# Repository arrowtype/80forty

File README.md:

# 80forty Keyboard

The utility of an 80% keyboard in a 40% form factor.

Inspired by the design of the [OP-1 Synthesizer](https://teenage.engineering/store/op-1-field/), the explorative spirit of the 40% & 30% keyboard community (especially boards like ChonkyKong, CutiePie, and Ortho Cajal), and the tactile reference points and minimized finger-travel of many split, ergonomic keyboards. The 80forty was partly motivated by the appearance of [Deadline Studio DOYS keycaps](https://deadline.space/products/doys-keycaps), but it works with any MX-compatible keycaps.

The 80forty has a layout that is ortholinear and minimal, but still retains the keys that are helpful for everyday computing and specialized tasks like graphic design applications (i.e. arrow keys, bottom mod keys, and outer columns allowing for e.g. dedicated shift and backspace keys). It also allows either a knob or a 2x2 macropad above the arrow keys.

Supports low-profile KS33 switches (with hotswap sockets) as well as MX switches (soldered/mill-maxed).

## V1 Case Designs

Version 1 uses either a stacked acrylic or ”skeleton” FR4 plate design.

While the PCB supports either KS33 or MX switches, the current case designs have only been settled for the KS33 switches. MX switches require more space, and would likely require larger middle case layers.

### Stacked Acrylic Case

This case uses the standard FR4 top plate of the 80forty, and sandwiches it in a few layers of 5mm, lasercut acrylic.

### Skeleton FR4 Case

This case uses the standard FR4 top and bottom plates of the 80forty, with standoffs providing middle separation for the switches.

## Configuration Options

Configurable with either 1 large knob or 4 macro keys.

## Keymaps

80forty is configurable in Vial, so the keymap can be whatever you want! However, here are two example layouts to show what might be common approaches to such a keyboard.

The 2-unit spacebars are intended to serve double duty: to input `Space` when tapped, or to shift to respective layers when held.

Vial/QMK also allow for “key combos.” So, for instance, it is possible to forgo a dedicated `Escape` key and instead assign this to `Tilde` + `Q`.

## Future Vision

The project was conceived to allow a sleek, low-profile, CNC aluminum case design. This is still a goal, but there is no current timeline for this version.

In the slightly nearer term, the intention is to prototype this case with 3D printing. If anyone out there is interested in creating this 3D case and contributing it to the project, let us know in the issues or in a pull request!

## Credits

Concept, layout, case design, and PCB graphics by Stephen Nixon / ArrowType.

Engineering, code, and PCB specifications and ordering by Noah Kiser / Kiser Designs.

## To be continued!

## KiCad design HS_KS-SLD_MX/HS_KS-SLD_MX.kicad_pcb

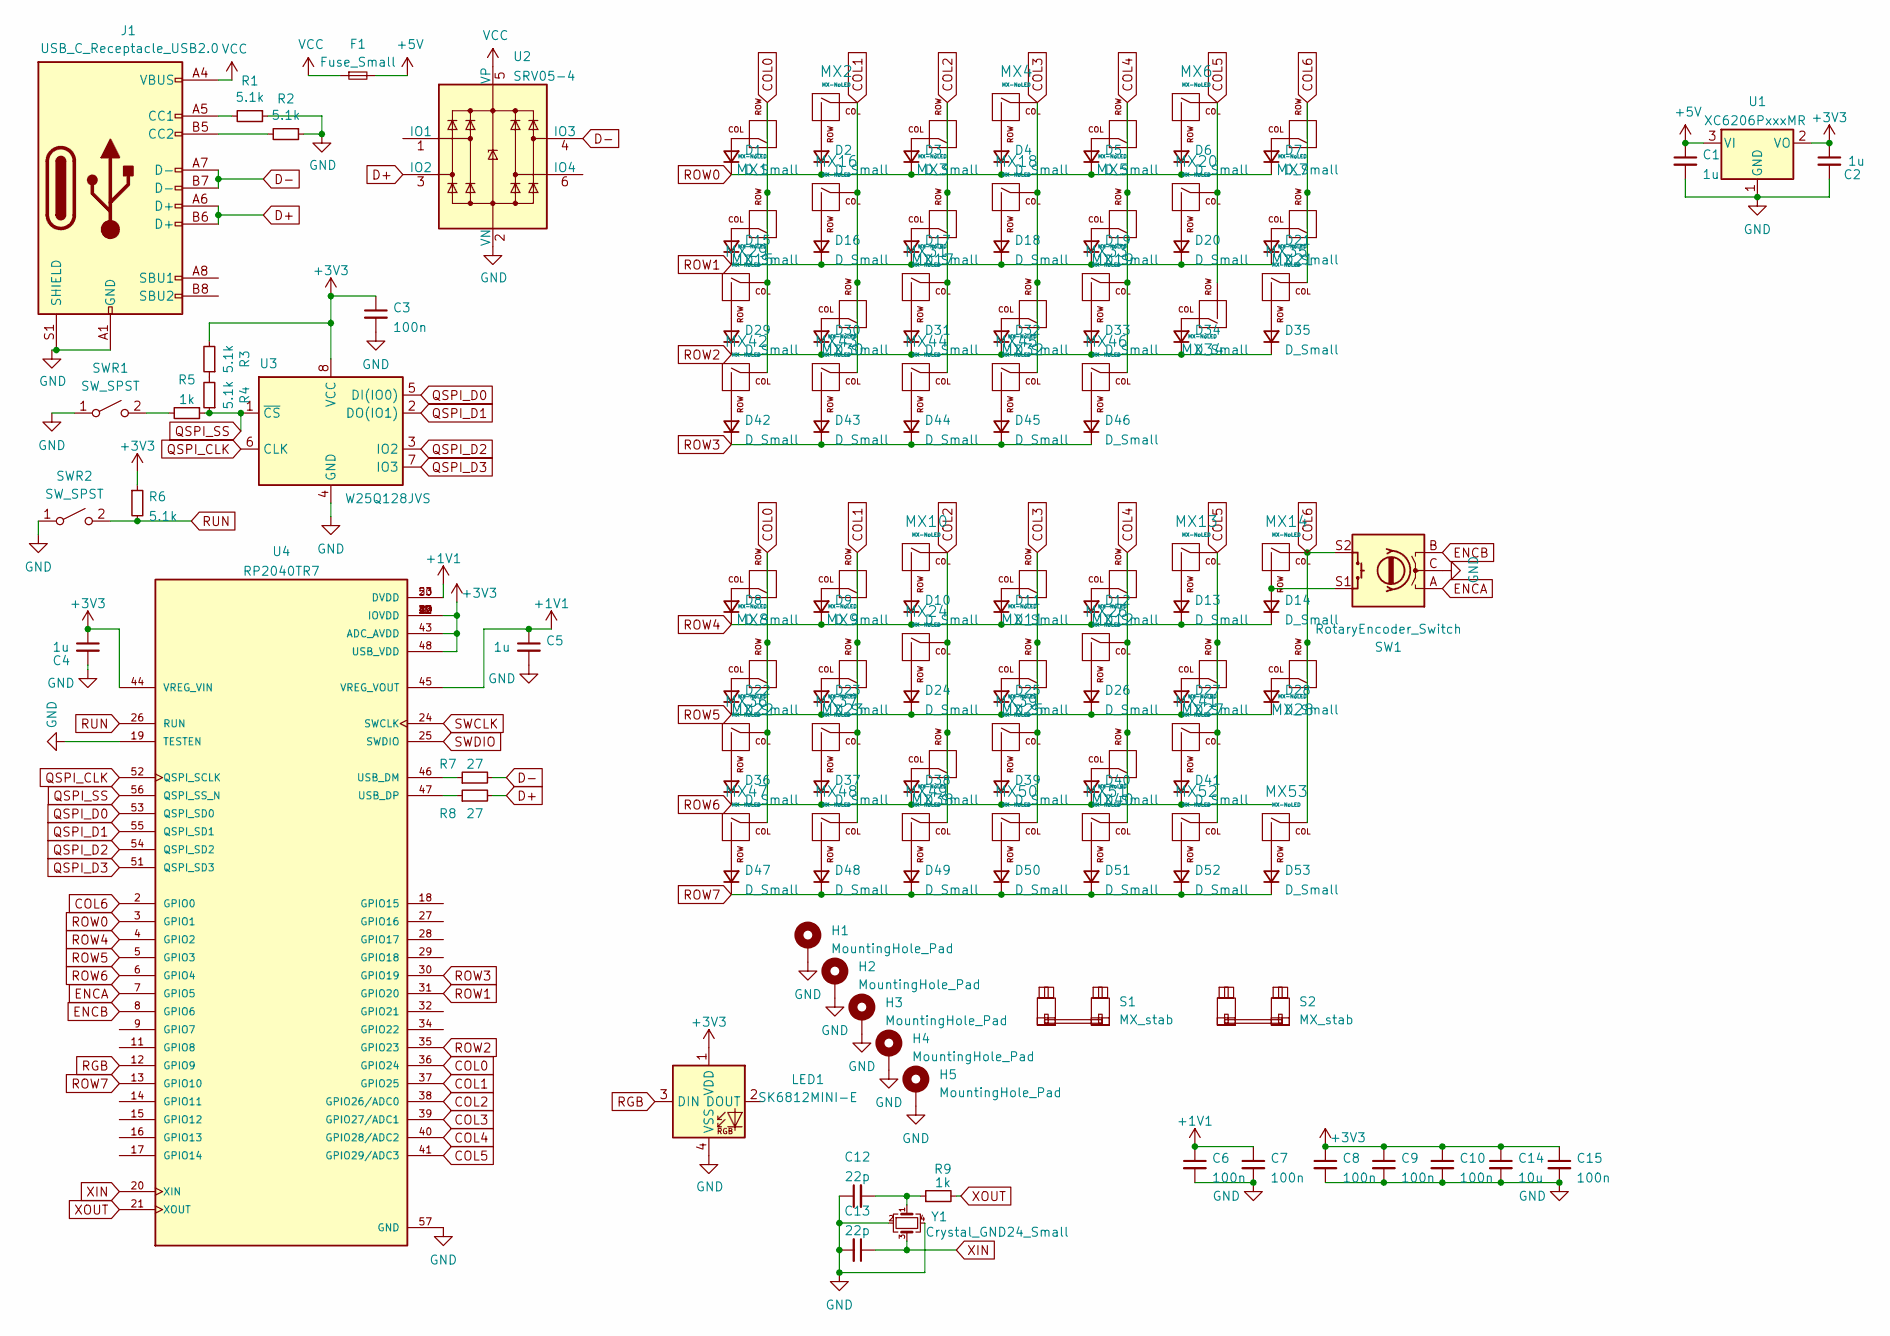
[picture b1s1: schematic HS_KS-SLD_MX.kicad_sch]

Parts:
C1, C2, C4, C5: 1u; C_0402_1005Metric
C3, C6, C7, C8, C9, C10, C15: 100n; C_0402_1005Metric
C12, C13: 22p; C_0402_1005Metric
C14: 10u; C_0402_1005Metric
D1, D2, D3, D4, D5, D6, D7, D8, D9, D10, D11, D12, D13, D14, D15, D16, D17, D18, D19, D20, D21, D22, D23, D24, D25, D26, D27, D28, D29, D30, D31, D32, D33, D34, D35, D36, D37, D38, D39, D40, D41, D42, D43, D44, D45, D46, D47, D48, D49, D50, D51, D52, D53: D_Small; D_SOD-123
F1: Fuse_Small; Fuse_1206_3216Metric
H1, H2, H3, H4, H5: MountingHole_Pad; MountingHole_2.2mm_M2_Pad_TopOnly
J1: USB_C_Receptacle_USB2.0; USB_C_Receptacle_HRO_TYPE-C-31-M-12
LED1: SK6812MINI-E; LED_6028R
MX1, MX2, MX3, MX4, MX5, MX6, MX7, MX8, MX9, MX10, MX11, MX12, MX13, MX14, MX15, MX16, MX17, MX18, MX19, MX20, MX21, MX22, MX23, MX24, MX25, MX26, MX27, MX28, MX29, MX30, MX31, MX32, MX33, MX34, MX35, MX36, MX37, MX38, MX39, MX40, MX41, MX42, MX43, MX44, MX45, MX46, MX47, MX48, MX49, MX50, MX51, MX52, MX53: MX-NoLED; HS-KS-33_Soldered-MX
R1, R2, R3, R4, R6: 5.1k; R_0402_1005Metric
R5, R9: 1k; R_0402_1005Metric
R7, R8: 27; R_0402_1005Metric
S1, S2: MX_stab; STAB_MX_P_2u
SW1: RotaryEncoder_Switch; RotaryEncoder_Alps_EC11E-Switch_Vertical_H20mm
SWR1, SWR2: SW_SPST; SW_SPST_TL3342
U1: XC6206PxxxMR; SOT-23
U2: SRV05-4; SOT-23-6-routable
U3: W25Q128JVS; SOIC-8_5.23x5.23mm_P1.27mm
U4: RP2040TR7; QFN-56-1EP_7x7mm_P0.4mm_EP3.2x3.2mm; PARTREV 1.7.1
Y1: Crystal_GND24_Small; Crystal_SMD_3225-4Pin_3.2x2.5mm

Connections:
+1V1: C5.1, C6.1, C7.1, U4.23 (DVDD), U4.45 (VREG_VOUT), U4.50 (DVDD)
+3V3: C2.1, C3.1, C4.1, C8.1, C9.1, C10.1, C14.1, C15.1, LED1.1 (VDD), R3.2, R6.1, U1.2 (VO), U3.8 (VCC), U4.1 (IOVDD), U4.10 (IOVDD), U4.22 (IOVDD), U4.33 (IOVDD), U4.42 (IOVDD), U4.43 (ADC_AVDD), U4.44 (VREG_VIN), U4.48 (USB_VDD), U4.49 (IOVDD)
+5V: C1.1, F1.2, U1.3 (VI)
COL0: MX1.2 (ROW), MX8.2 (ROW), MX15.2 (ROW), MX22.2 (ROW), MX29.1 (COL), MX36.1 (COL), MX42.1 (COL), MX47.1 (COL), U4.36 (GPIO24)
COL1: MX2.1 (COL), MX9.2 (ROW), MX16.1 (COL), MX23.2 (ROW), MX30.2 (ROW), MX37.1 (COL), MX43.1 (COL), MX48.1 (COL), U4.37 (GPIO25)
COL2: MX3.2 (ROW), MX10.1 (COL), MX17.2 (ROW), MX24.1 (COL), MX31.1 (COL), MX38.2 (ROW), MX44.1 (COL), MX49.1 (COL), U4.38 (GPIO26/ADC0)
COL3: MX4.1 (COL), MX11.2 (ROW), MX18.1 (COL), MX25.2 (ROW), MX32.2 (ROW), MX39.1 (COL), MX45.1 (COL), MX50.1 (COL), U4.39 (GPIO27/ADC1)
COL4: MX5.2 (ROW), MX12.2 (ROW), MX19.2 (ROW), MX26.1 (COL), MX33.1 (COL), MX40.2 (ROW), MX46.1 (COL), MX51.1 (COL), U4.40 (GPIO28/ADC2)
COL5: MX6.1 (COL), MX13.1 (COL), MX20.1 (COL), MX27.2 (ROW), MX34.2 (ROW), MX41.1 (COL), MX52.1 (COL), U4.41 (GPIO29/ADC3)
COL6: MX7.2 (ROW), MX14.1 (COL), MX21.2 (ROW), MX28.2 (ROW), MX35.1 (COL), MX53.1 (COL), SW1.S2, U4.2 (GPIO0)
D+: J1.A6 (D+), J1.B6 (D+), R8.2, U2.3 (IO2)
D-: J1.A7 (D-), J1.B7 (D-), R7.2, U2.4 (IO3)
ENCA: SW1.A, U4.7 (GPIO5)
ENCB: SW1.B, U4.8 (GPIO6)
GND: C1.2, C2.2, C3.2, C4.2, C5.2, C6.2, C7.2, C8.2, C9.2, C10.2, C12.1, C13.2, C14.2, C15.2, H1.1, H2.1, H3.1, H4.1, H5.1, J1.A1 (GND), J1.A12 (GND), J1.B1 (GND), J1.B12 (GND), J1.S1 (SHIELD), LED1.4 (VSS), R1.1, R2.1, SW1.C, SWR1.1 (A), SWR2.1 (A), U1.1 (GND), U2.2 (VN), U3.4 (GND), U4.19 (TESTEN), U4.57 (GND), Y1.2, Y1.4
unnamed: C12.2, R9.1, Y1.1
unnamed: D1.2 (A), MX1.1 (COL)
unnamed: D2.2 (A), MX2.2 (ROW)
unnamed: D3.2 (A), MX3.1 (COL)
unnamed: D4.2 (A), MX4.2 (ROW)
unnamed: D5.2 (A), MX5.1 (COL)
unnamed: D6.2 (A), MX6.2 (ROW)
unnamed: D7.2 (A), MX7.1 (COL)
unnamed: D8.2 (A), MX8.1 (COL)
unnamed: D9.2 (A), MX9.1 (COL)
unnamed: D10.2 (A), MX10.2 (ROW)
unnamed: D11.2 (A), MX11.1 (COL)
unnamed: D12.2 (A), MX12.1 (COL)
unnamed: D13.2 (A), MX13.2 (ROW)
unnamed: D14.2 (A), MX14.2 (ROW), SW1.S1
unnamed: D15.2 (A), MX15.1 (COL)
unnamed: D16.2 (A), MX16.2 (ROW)
unnamed: D17.2 (A), MX17.1 (COL)
unnamed: D18.2 (A), MX18.2 (ROW)
unnamed: D19.2 (A), MX19.1 (COL)
unnamed: D20.2 (A), MX20.2 (ROW)
unnamed: D21.2 (A), MX21.1 (COL)
unnamed: D22.2 (A), MX22.1 (COL)
unnamed: D23.2 (A), MX23.1 (COL)
unnamed: D24.2 (A), MX24.2 (ROW)
unnamed: D25.2 (A), MX25.1 (COL)
unnamed: D26.2 (A), MX26.2 (ROW)
unnamed: D27.2 (A), MX27.1 (COL)
unnamed: D28.2 (A), MX28.1 (COL)
unnamed: D29.2 (A), MX29.2 (ROW)
unnamed: D30.2 (A), MX30.1 (COL)
unnamed: D31.2 (A), MX31.2 (ROW)
unnamed: D32.2 (A), MX32.1 (COL)
unnamed: D33.2 (A), MX33.2 (ROW)
unnamed: D34.2 (A), MX34.1 (COL)
unnamed: D35.2 (A), MX35.2 (ROW)
unnamed: D36.2 (A), MX36.2 (ROW)
unnamed: D37.2 (A), MX37.2 (ROW)
unnamed: D38.2 (A), MX38.1 (COL)
unnamed: D39.2 (A), MX39.2 (ROW)
unnamed: D40.2 (A), MX40.1 (COL)
unnamed: D41.2 (A), MX41.2 (ROW)
unnamed: D42.2 (A), MX42.2 (ROW)
unnamed: D43.2 (A), MX43.2 (ROW)
unnamed: D44.2 (A), MX44.2 (ROW)
unnamed: D45.2 (A), MX45.2 (ROW)
unnamed: D46.2 (A), MX46.2 (ROW)
unnamed: D47.2 (A), MX47.2 (ROW)
unnamed: D48.2 (A), MX48.2 (ROW)
unnamed: D49.2 (A), MX49.2 (ROW)
unnamed: D50.2 (A), MX50.2 (ROW)
unnamed: D51.2 (A), MX51.2 (ROW)
unnamed: D52.2 (A), MX52.2 (ROW)
unnamed: D53.2 (A), MX53.2 (ROW)
unnamed: J1.A5 (CC1), R1.2
unnamed: J1.B5 (CC2), R2.2
unnamed: R3.1, R4.2
unnamed: R5.2, SWR1.2 (B)
unnamed: R7.1, U4.46 (USB_DM)
unnamed: R8.1, U4.47 (USB_DP)
QSPI_CLK: U3.6 (CLK), U4.52 (QSPI_SCLK)
QSPI_D0: U3.5 (DI(IO0)), U4.53 (QSPI_SD0)
QSPI_D1: U3.2 (DO(IO1)), U4.55 (QSPI_SD1)
QSPI_D2: U3.3 (IO2), U4.54 (QSPI_SD2)
QSPI_D3: U3.7 (IO3), U4.51 (QSPI_SD3)
QSPI_SS: R4.1, R5.1, U3.1 (~CS), U4.56 (QSPI_SS_N)
RGB: LED1.3 (DIN), U4.12 (GPIO9)
ROW0: D1.1 (K), D2.1 (K), D3.1 (K), D4.1 (K), D5.1 (K), D6.1 (K), D7.1 (K), U4.3 (GPIO1)
ROW1: D15.1 (K), D16.1 (K), D17.1 (K), D18.1 (K), D19.1 (K), D20.1 (K), D21.1 (K), U4.31 (GPIO20)
ROW2: D29.1 (K), D30.1 (K), D31.1 (K), D32.1 (K), D33.1 (K), D34.1 (K), D35.1 (K), U4.35 (GPIO23)
ROW3: D42.1 (K), D43.1 (K), D44.1 (K), D45.1 (K), D46.1 (K), U4.30 (GPIO19)
ROW4: D8.1 (K), D9.1 (K), D10.1 (K), D11.1 (K), D12.1 (K), D13.1 (K), D14.1 (K), U4.4 (GPIO2)
ROW5: D22.1 (K), D23.1 (K), D24.1 (K), D25.1 (K), D26.1 (K), D27.1 (K), D28.1 (K), U4.5 (GPIO3)
ROW6: D36.1 (K), D37.1 (K), D38.1 (K), D39.1 (K), D40.1 (K), D41.1 (K), U4.6 (GPIO4)
ROW7: D47.1 (K), D48.1 (K), D49.1 (K), D50.1 (K), D51.1 (K), D52.1 (K), D53.1 (K), U4.13 (GPIO10)
RUN: R6.2, SWR2.2 (B), U4.26 (RUN)
SWCLK: U4.24 (SWCLK)
SWDIO: U4.25 (SWDIO)
VCC: F1.1, J1.A4 (VBUS), J1.A9 (VBUS), J1.B4 (VBUS), J1.B9 (VBUS), U2.5 (VP)
XIN: C13.1, U4.20 (XIN), Y1.3
XOUT: R9.2, U4.21 (XOUT)

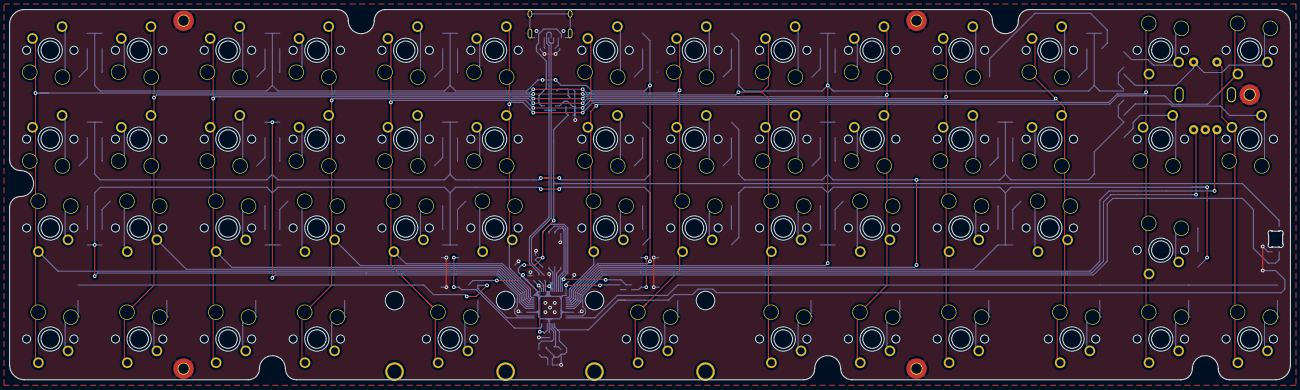
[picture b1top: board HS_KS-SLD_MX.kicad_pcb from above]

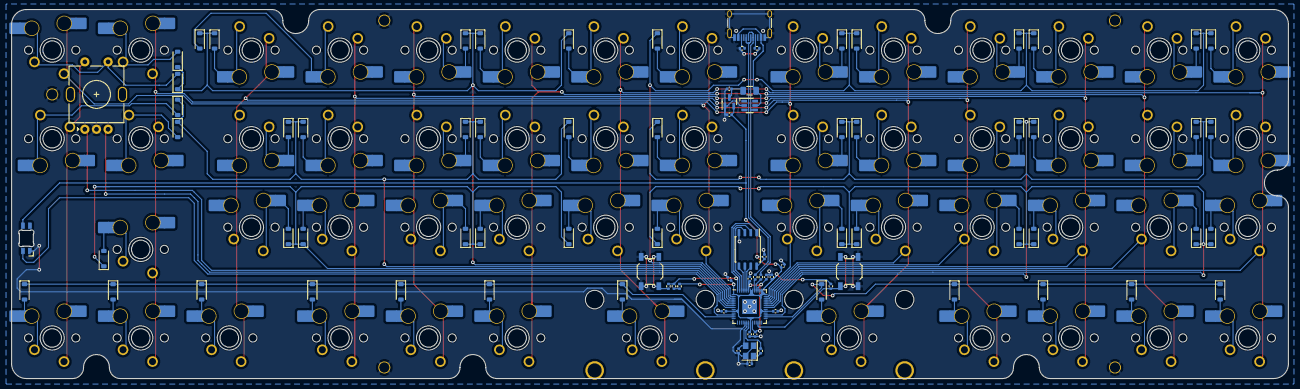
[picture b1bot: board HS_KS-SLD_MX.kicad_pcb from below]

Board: 2 copper layers, 274.6 x 79.4 mm, 147 parts (89 on the bottom side), 94 nets.

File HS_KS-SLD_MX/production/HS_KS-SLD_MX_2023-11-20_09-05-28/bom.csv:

Designator,Footprint,Quantity,Value,LCSC Part #
"C1, C2, C4, C5",402,4,1u,C52923
"C10, C15, C3, C6, C7, C8, C9",402,7,100n,C1525
"C12, C13",402,2,22p,C1562
C14,402,1,10u,C15525
"D1, D10, D11, D12, D13, D14, D15, D16, D17, D18, D19, D2, D20, D21, D22, D23, D24, D25, D26, D27, D28, D29, D3, D30, D31, D32, D33, D34, D35, D36, D37, D38, D39, D4, D40, D41, D42, D43, D44, D45, D46, D47, D48, D49, D5, D50, D51, D52, D53, D6, D7, D8, D9",D_SOD-123,53,D_Small,C81598
F1,1206,1,Fuse_Small,C883133
J1,USB_C_Receptacle_HRO_TYPE-C-31-M-12,1,USB_C_Receptacle_USB2.0,C165948
LED1,LED_6028R,1,SK6812MINI-E,C5149201
"R1, R2, R3, R4, R6",402,5,5.1k,C25905
"R5, R9",402,2,1k,C11702
"R7, R8",402,2,27,C25092
"SWR1, SWR2",SW_SPST_TL3342,2,SW_SPST,C318884
U1,SOT-23,1,XC6206PxxxMR,C5446
U2,SOT-23-6-routable,1,SRV05-4,C85364
U3,SOIC-8_5.23x5.23mm_P1.27mm,1,W25Q128JVS,C97521
U4,QFN-56-1EP_7x7mm_P0.4mm_EP3.2x3.2mm,1,RP2040TR7,C2040
Y1,Crystal_SMD_3225-4Pin_3.2x2.5mm,1,Crystal_GND24_Small,C2040

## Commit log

2023-08-02 Initial commit of PCB source, unfinished
2023-08-03 Update LICENSE
2023-08-03 routed rows
2023-08-03 A bit more routing
2023-08-03 almost done with columns
2023-08-03 add .gitignore to ignore .DS_Store
2023-08-03 Just a few more connections
2023-08-04 Completed MX PCB
2023-08-06 Add GLP_PCB, name fix
2023-08-23 lo-pro test production
2023-08-25 some changes
2023-10-31 add mx+gs hotswap PCB
2023-11-02 Routed, will DRC tomorrow
2023-11-03 remove unneeded PCB options
2023-11-05 add br00tal artwork
2023-11-05 tweak artwork for slightly better letter spacing
2023-11-05 add quick image of approximate artwork placement on PCB
2023-11-05 tweak artwork again
2023-11-06 Add SVGs
2023-11-12 add design for artwork placement
2023-11-12 outline text in artwork
2023-11-12 Move logos to Layer 1
2023-11-13 Added WIP graphics to PCB (and dirty Inkscape SVG converted from PDF)
2023-11-20 add PCB prod files, clean up silkscreen
2023-11-20 update bom
2023-11-21 Add v1.0 mockups
2023-11-21 Tweak v1 mockups
2023-11-21 add skeleton case files
2024-01-13 add images
2024-01-29 add hero image
2024-01-29 Update README.md with new hero image
2024-02-05 rename folder for skeleton case files
2024-02-05 add starter files for acrylic case
